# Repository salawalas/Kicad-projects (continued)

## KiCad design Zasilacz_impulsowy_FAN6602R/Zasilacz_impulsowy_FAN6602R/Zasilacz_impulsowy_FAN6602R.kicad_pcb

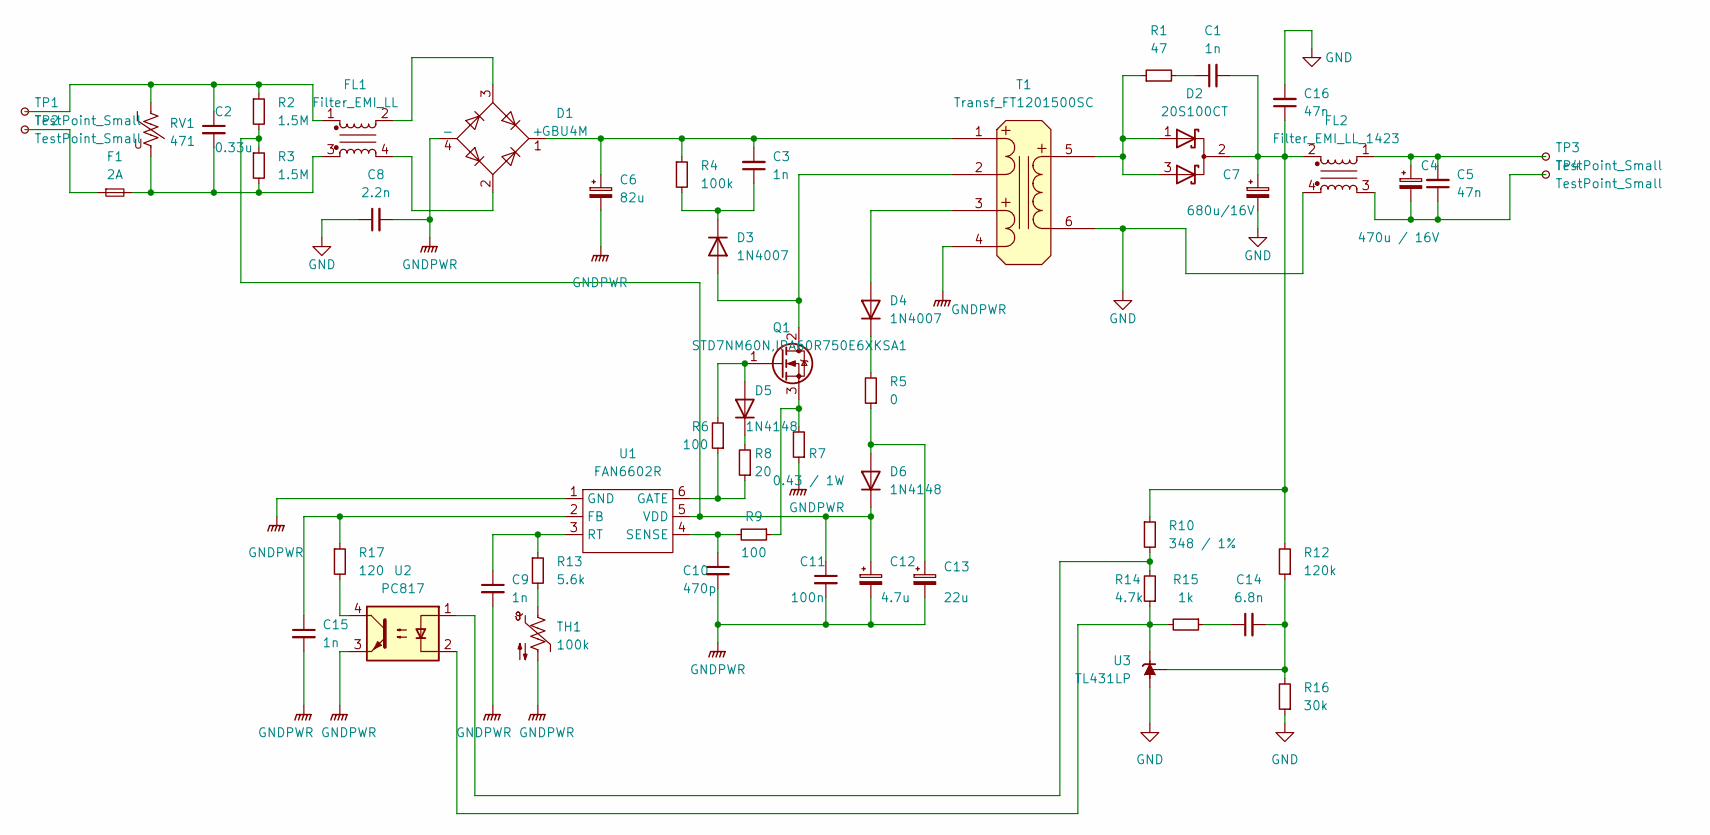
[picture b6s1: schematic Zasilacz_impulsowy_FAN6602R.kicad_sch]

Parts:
C1: 1n; C_1210_3225Metric
C2: 0.33u; C_Rect_L18.0mm_W7.0mm_P15.00mm_FKS3_FKP3
C3: 1n; C_Axial_L5.1mm_D3.1mm_P10.00mm_Horizontal
C4: 470u / 16V; CP_Radial_D8.0mm_P3.50mm
C5, C16: 47n; C_1206_3216Metric
C6: 82u; CP_Radial_D13.0mm_P7.50mm
C7: 680u/16V; CP_Radial_D10.0mm_P3.50mm
C8: 2.2n; C_Axial_L5.1mm_D3.1mm_P10.00mm_Horizontal
C9, C15: 1n; C_0805_2012Metric
C10: 470p; C_0805_2012Metric
C11: 100n; C_0805_2012Metric
C12: 4.7u; CP_Radial_D5.0mm_P2.50mm
C13: 22u; CP_Radial_D5.0mm_P2.50mm
C14: 6.8n; C_1206_3216Metric
D1: GBU4M; Diode_Bridge_Vishay_GBL
D2: 20S100CT; TO-220-3_Vertical
D3: 1N4007; D_DO-41_SOD81_P15mm_Horizontal
D4: 1N4007; D_DO-41_SOD81_P10.16mm_Horizontal
D5, D6: 1N4148; D_DO-35_SOD27_P7.62mm_Horizontal
F1: 2A; R_Axial_DIN0309_L9.0mm_D3.2mm_P5.08mm_Vertical
FL1: Filter_EMI_LL; Fitr_EMI_FA-N12W1051-REG-1
FL2: Filter_EMI_LL_1423; Filtr_EMI_toroid
Q1: STD7NM60N,IPA60R750E6XKSA1; TO-220F-3_Vertical
R1: 47; R_1206_3216Metric
R2, R3: 1.5M; R_1210_3225Metric
R4: 100k; R_1210_3225Metric
R5: 0; R_Axial_DIN0204_L3.6mm_D1.6mm_P7.62mm_Horizontal
R6, R9: 100; R_0805_2012Metric
R7: 0.43 / 1W; R_Axial_DIN0309_L9.0mm_D3.2mm_P2.54mm_Vertical
R8: 20; R_0805_2012Metric
R10: 348 / 1%; R_0805_2012Metric
R12: 120k; R_1206_3216Metric
R13: 5.6k; R_0805_2012Metric
R14: 4.7k; R_0805_2012Metric
R15: 1k; R_0805_2012Metric
R16: 30k; R_0805_2012Metric
R17: 120; R_0805_2012Metric
RV1: 471; RV_Disc_D12mm_W3.9mm_P7.5mm
T1: Transf_FT1201500SC
TH1: 100k; C_Disc_D3.4mm_W2.1mm_P2.50mm
TP1, TP2, TP3, TP4: TestPoint_Small; Pin_D1.3mm_L11.0mm
U1: FAN6602R; SOT-23-6_Handsoldering
U2: PC817; DIP-4_W7.62mm
U3: TL431LP; TO-92_Inline

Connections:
GND: C7.2, C8.1, C16.2, FL2.4, R16.1, T1.6 (S-), U3.2 (A)
GNDPWR: C6.2, C8.2, C9.2, C10.2, C11.2, C12.2, C13.2, C15.2, D1.4 (-), R7.1, T1.4 (P2-), TH1.2, U1.1 (GND), U2.3
unnamed: C1.1, R1.2
unnamed: C1.2, C7.1, C16.1, D2.2 (A), FL2.2, R10.1, R12.2
unnamed: C2.1, FL1.1, R2.1, RV1.1, TP1.1
unnamed: C2.2, F1.2, FL1.3, R3.2, RV1.2
unnamed: C3.1, D3.1 (K), R4.2
unnamed: C3.2, C6.1, D1.1 (+), R4.1, T1.1 (P1+)
unnamed: C4.1, C5.2, FL2.1, TP3.1
unnamed: C4.2, C5.1, FL2.3, TP4.1
unnamed: C9.1, R13.1, U1.3 (RT)
unnamed: C10.1, R9.2, U1.4 (SENSE)
unnamed: C11.1, C12.1, D6.1 (K), R2.2, R3.1, U1.5 (VDD)
unnamed: C13.1, D6.2 (A), R5.1
unnamed: C14.1, R15.1
unnamed: C14.2, R12.1, R16.2, U3.1 (REF)
unnamed: C15.1, R17.1, U1.2 (FB)
unnamed: D1.2, FL1.4
unnamed: D1.3, FL1.2
unnamed: D2.1 (K), D2.3 (K), R1.1, T1.5 (S+)
unnamed: D3.2 (A), Q1.2 (D), T1.2 (P1-)
unnamed: D4.1 (K), R5.2
unnamed: D4.2 (A), T1.3 (P2+)
unnamed: D5.1 (K), R8.2
unnamed: D5.2 (A), Q1.1 (G), R6.2
unnamed: F1.1, TP2.1
unnamed: Q1.3 (S), R7.2, R9.1
unnamed: R6.1, R8.1, U1.6 (GATE)
unnamed: R10.2, R14.2, U2.1
unnamed: R13.2, TH1.1
unnamed: R14.1, R15.2, U2.2, U3.3 (K)
unnamed: R17.2, U2.4

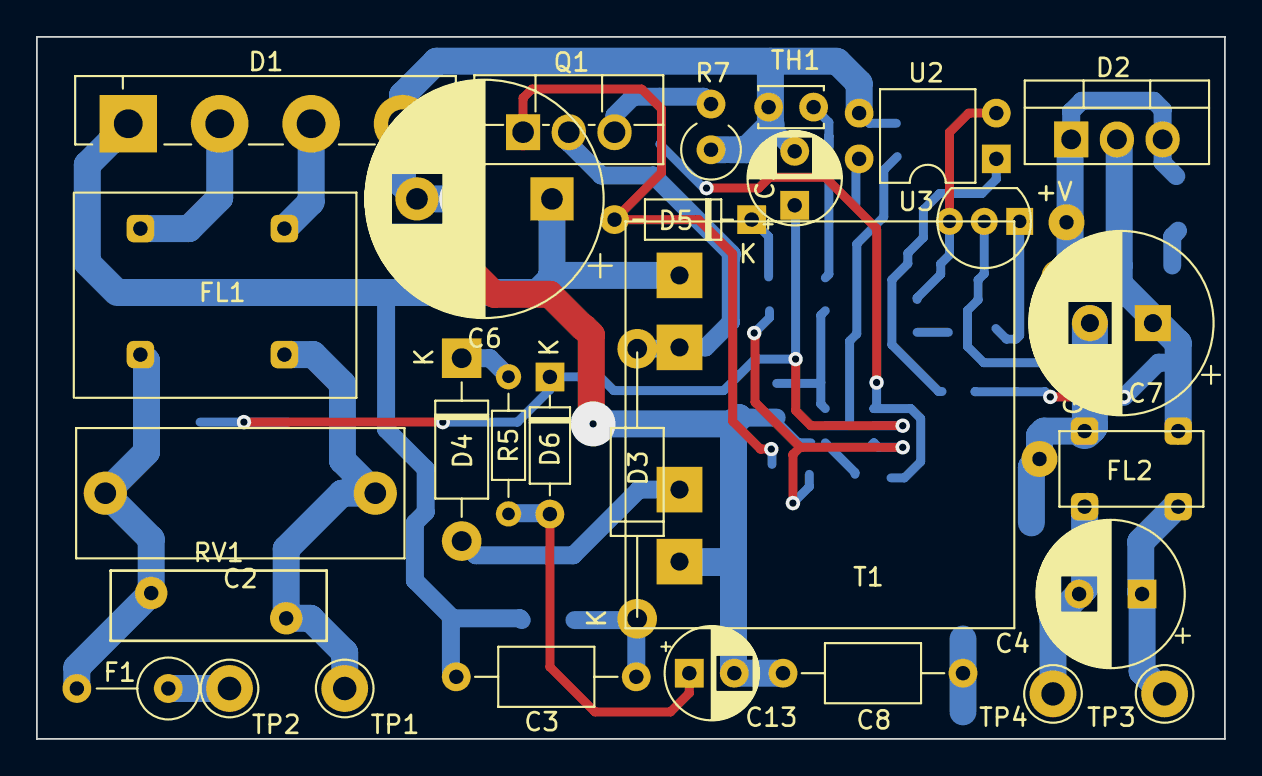
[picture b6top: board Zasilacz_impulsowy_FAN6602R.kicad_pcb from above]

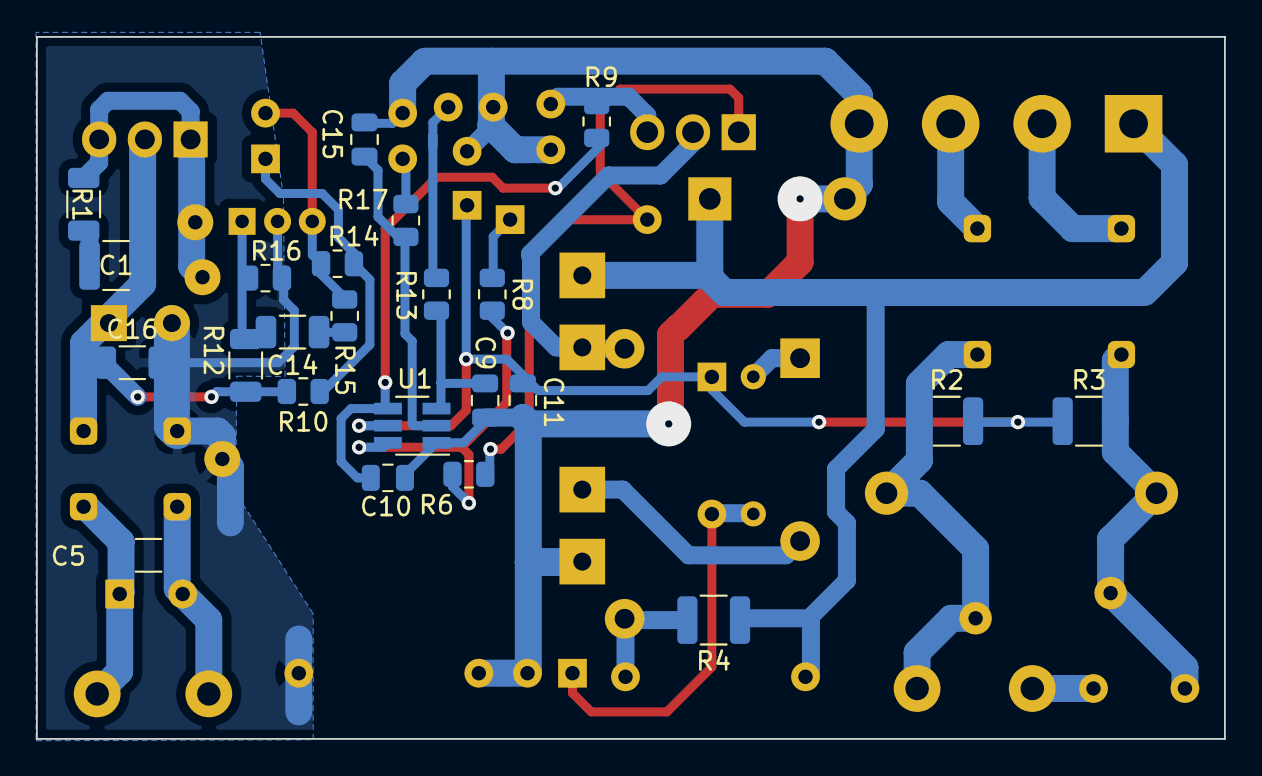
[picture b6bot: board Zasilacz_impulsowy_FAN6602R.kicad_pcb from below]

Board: 2 copper layers, 66.0 x 39.0 mm, 52 parts (23 on the bottom side), 32 nets.

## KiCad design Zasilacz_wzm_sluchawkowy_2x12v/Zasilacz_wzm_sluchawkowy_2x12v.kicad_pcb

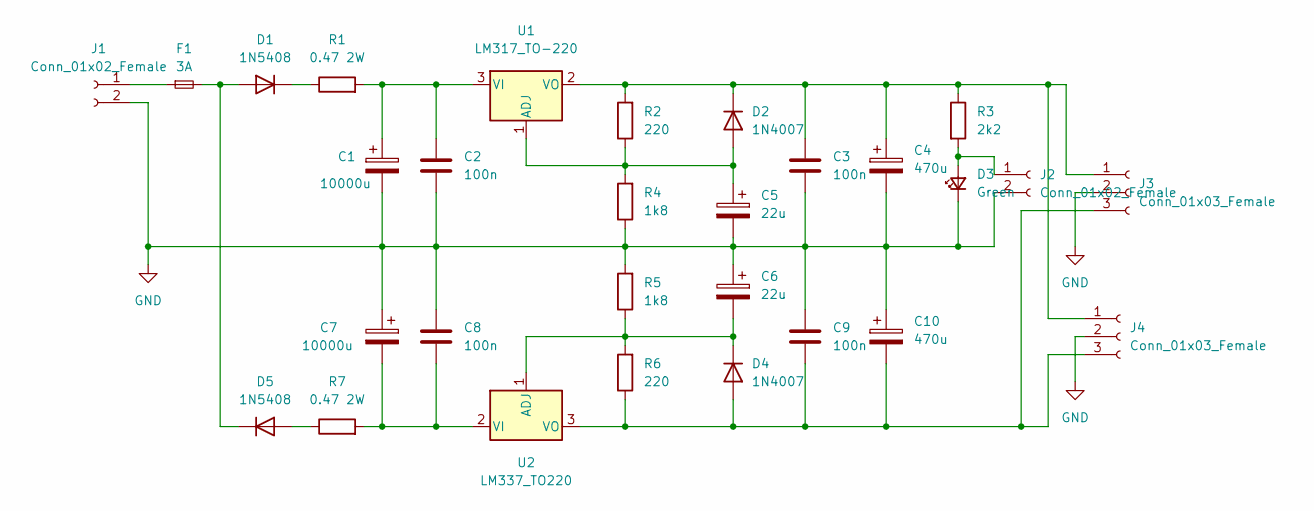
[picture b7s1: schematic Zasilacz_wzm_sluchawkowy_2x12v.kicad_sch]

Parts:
C1, C7: 10000u; CP_Radial_D18.0mm_P7.50mm
C2, C3, C8, C9: 100n; C_Rect_L9.0mm_W3.3mm_P7.50mm_MKT
C4, C10: 470u; CP_Radial_D12.5mm_P5.00mm
C5, C6: 22u; CP_Radial_Tantal_D6.0mm_P5.00mm
D1, D5: 1N5408; D_DO-201AD_P15.24mm_Horizontal
D2, D4: 1N4007; D_DO-41_SOD81_P10.16mm_Horizontal
D3: Green; LED_D5.0mm
F1: 3A; Fuseholder_Littelfuse_445_030_series_5x20mm
J1: Conn_01x02_Female; Molex_KK-396_A-41791-0002_1x02_P3.96mm_Vertical
J2: Conn_01x02_Female; JST_PH_B2B-PH-K_1x02_P2.00mm_Vertical
J3, J4: Conn_01x03_Female; Molex_KK-254_AE-6410-03A_1x03_P2.54mm_Vertical
R1, R7: 0.47 2W; R_Axial_Power_L20.0mm_W6.4mm_P22.40mm
R2, R6: 220; R_Axial_DIN0207_L6.3mm_D2.5mm_P10.16mm_Horizontal
R3: 2k2; R_Axial_DIN0207_L6.3mm_D2.5mm_P10.16mm_Horizontal
R4, R5: 1k8; R_Axial_DIN0207_L6.3mm_D2.5mm_P10.16mm_Horizontal
U1: LM317_TO-220; TO-220-3_Vertical
U2: LM337_TO220; TO-220-3_Vertical

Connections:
GND: C1.2, C2.2, C3.2, C4.2, C5.2, C6.1, C7.1, C8.1, C9.1, C10.1, D3.1 (K), J1.2, J2.2, J3.2, J4.2, R4.1, R5.2
unnamed: C1.1, C2.1, R1.2, U1.3 (VI)
unnamed: C3.1, C4.1, D2.1 (K), J3.1, J4.1, R2.2, R3.1, U1.2 (VO)
unnamed: C5.1, D2.2 (A), R2.1, R4.2, U1.1 (ADJ)
unnamed: C6.2, D4.1 (K), R5.1, R6.2, U2.1 (ADJ)
unnamed: C7.2, C8.2, R7.2, U2.2 (VI)
unnamed: C9.2, C10.2, D4.2 (A), J3.3, J4.3, R6.1, U2.3 (VO)
unnamed: D1.1 (K), R1.1
unnamed: D1.2 (A), D5.1 (K), F1.2
unnamed: D3.2 (A), J2.1, R3.2
unnamed: D5.2 (A), R7.1
unnamed: F1.1, J1.1

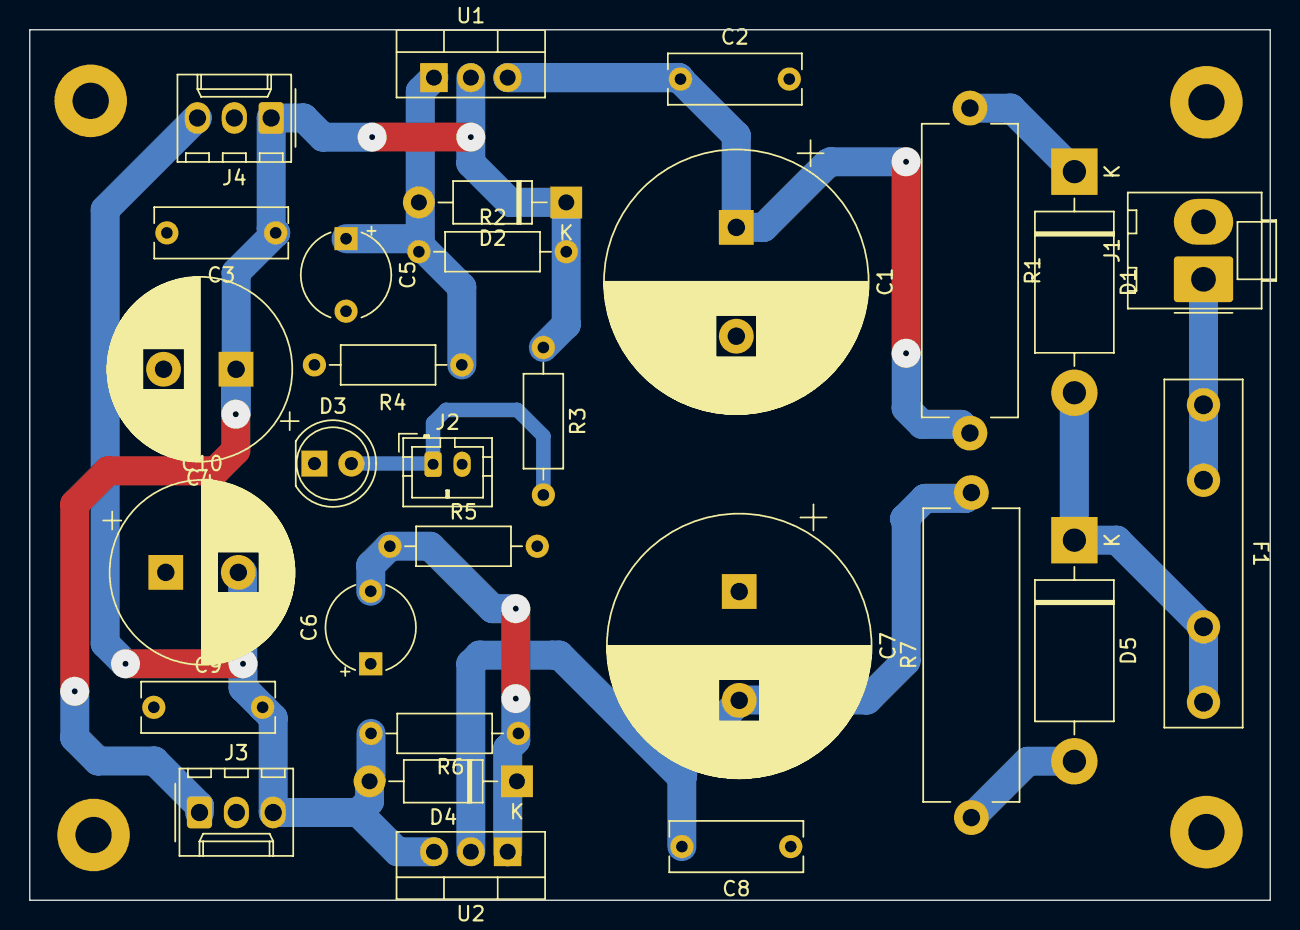
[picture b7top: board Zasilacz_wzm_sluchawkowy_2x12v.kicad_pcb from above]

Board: 2 copper layers, 85.5 x 60.0 mm, 29 parts (0 on the bottom side), 12 nets.
